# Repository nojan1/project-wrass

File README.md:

# Project Wrass

The purpose of Project Wrass is to develop the **Wrass 1**.

A 6502 based computer having the following specs.

* W65C02 running at 2Mhz
* Bankable RAM giving a total of approx 300KB of usable memory
* Expansion bus for up to 16 devices

> **Future specs**:  
>
> * VGA output of 640x480 with 256 colors
> * IO Card with W65C22 Vias and support for SPI
> * Support for SD cards on IO card
> * 8Mhz CPU clock speed
> * Global scroll registers for video
> * Sprites
> * 3 channel sound synthesizer

## Software

The 16KB ROM is bankable using an external switch. This allows the computer to run "2 sets" of software.

The existing one is a simple homebrew "monitor" giving access to simple read, write and jump commands.

> **Future**:  
> Support enhanced basic

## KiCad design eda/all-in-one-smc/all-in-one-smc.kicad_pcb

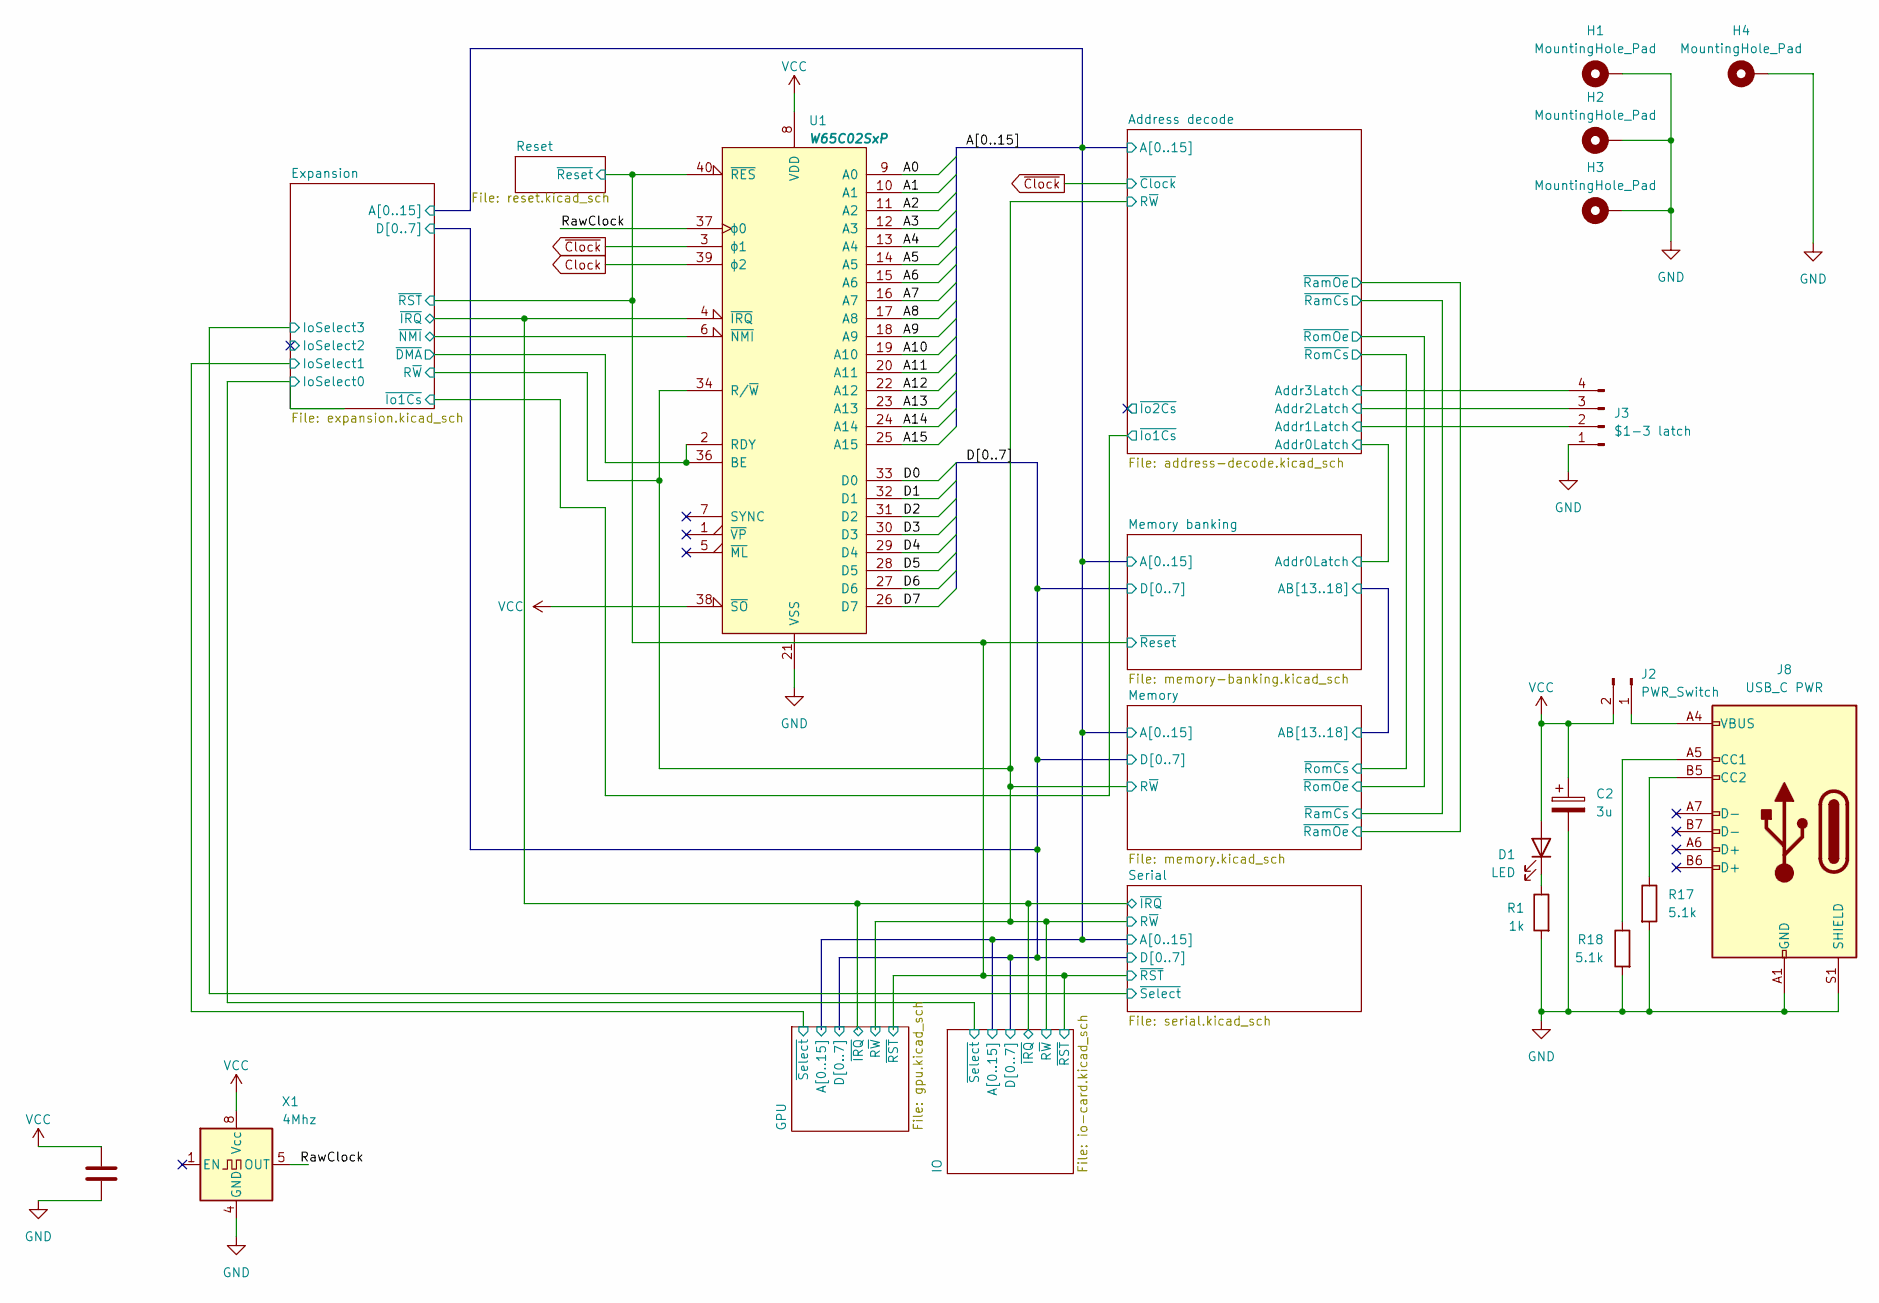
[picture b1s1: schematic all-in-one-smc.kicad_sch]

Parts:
C1: 100n; C_0805_2012Metric
C2: 3u; CP_Elec_8x5.4
D1: LED; LED_0805_2012Metric
H1, H2, H3, H4: MountingHole_Pad; MountingHole_2.5mm_Pad_Via
J2: PWR_Switch; PinHeader_1x02_P2.54mm_Vertical
J3: $1-3 latch; PinHeader_1x04_P2.54mm_Vertical
J8: USB_C PWR; USB_C_Receptacle_GCT_USB4105-xx-A_16P_TopMnt_Horizontal
R1: 1k; R_0805_2012Metric
R17, R18: 5.1k; R_0805_2012Metric
U1: W65C02SxP; PQFP-44_10x10mm_P0.8mm
X1: 4Mhz; Oscillator_DIP-8

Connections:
/A0: U1.9 (A0); also elsewhere on the board
/A1: U1.10 (A1); also elsewhere on the board
/A2: U1.11 (A2); also elsewhere on the board
/A3: U1.12 (A3); also elsewhere on the board
/A4: U1.13 (A4); also elsewhere on the board
/A5: U1.14 (A5); also elsewhere on the board
/A6: U1.15 (A6); also elsewhere on the board
/A7: U1.16 (A7); also elsewhere on the board
/A8: U1.17 (A8); also elsewhere on the board
/A9: U1.18 (A9); also elsewhere on the board
/A10: U1.19 (A10); also elsewhere on the board
/A11: U1.20 (A11); also elsewhere on the board
/A12: U1.22 (A12); also elsewhere on the board
/A13: U1.23 (A13); also elsewhere on the board
/A14: U1.24 (A14); also elsewhere on the board
/A15: U1.25 (A15); also elsewhere on the board
/Address decode/Addr1Latch: J3.2; also elsewhere on the board
/Address decode/Addr2Latch: J3.3; also elsewhere on the board
/Address decode/Addr3Latch: J3.4; also elsewhere on the board
/Address decode/R~W: U1.34 (R/~W); also elsewhere on the board
/D0: U1.33 (D0); also elsewhere on the board
/D1: U1.32 (D1); also elsewhere on the board
/D2: U1.31 (D2); also elsewhere on the board
/D3: U1.30 (D3); also elsewhere on the board
/D4: U1.29 (D4); also elsewhere on the board
/D5: U1.28 (D5); also elsewhere on the board
/D6: U1.27 (D6); also elsewhere on the board
/D7: U1.26 (D7); also elsewhere on the board
/Expansion/~DMA: U1.2 (RDY), U1.36 (BE); also elsewhere on the board
/Expansion/~IRQ: U1.4 (~IRQ); also elsewhere on the board
/Expansion/~NMI: U1.6 (~NMI); also elsewhere on the board
/Expansion/~RST: U1.40 (~RES); also elsewhere on the board
/RawClock: U1.37 (ϕ0), X1.5 (OUT)
Clock: U1.39 (ϕ2); also elsewhere on the board
unnamed: D1.1 (K), R1.1
unnamed: J2.1, J8.A4 (VBUS), J8.A9 (VBUS), J8.B4 (VBUS), J8.B9 (VBUS)
unnamed: J8.A5 (CC1), R18.1
unnamed: J8.B5 (CC2), R17.1
~Clock: U1.3 (ϕ1); also elsewhere on the board

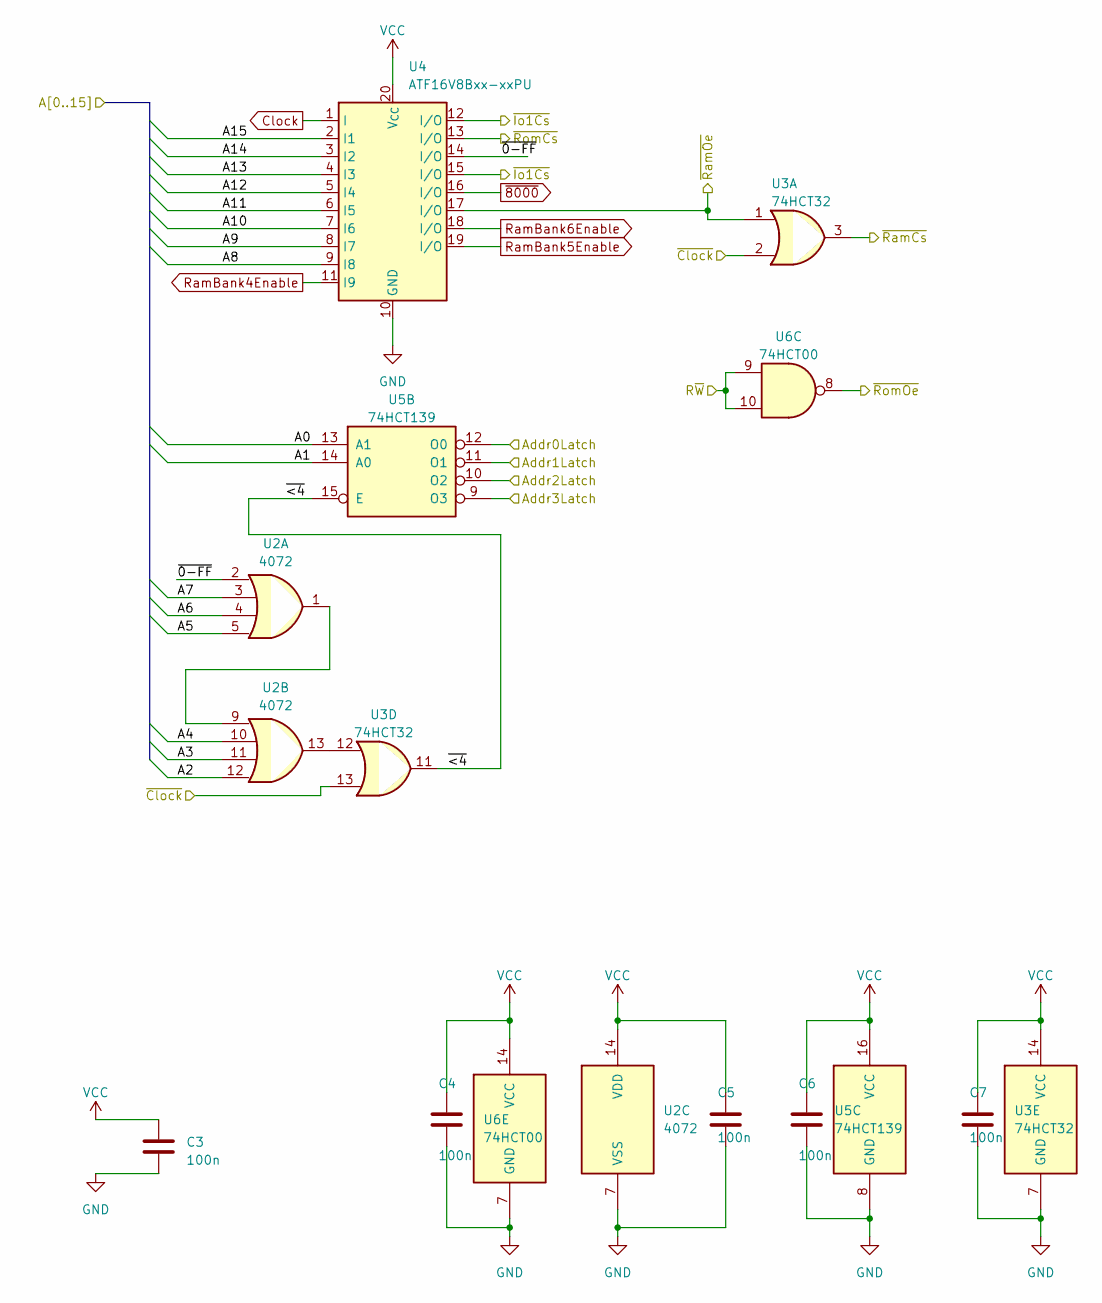
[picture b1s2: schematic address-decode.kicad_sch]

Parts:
C3, C4, C5, C6, C7: 100n; C_0805_2012Metric
U2: 4072; SOIC-14_3.9x8.7mm_P1.27mm
U3: 74HCT32; SOIC-14_3.9x8.7mm_P1.27mm
U4: ATF16V8Bxx-xxPU; DIP-20_W7.62mm_Socket
U5: 74HCT139; SOIC-16_3.9x9.9mm_P1.27mm
U6: 74HCT00; SOIC-14_3.9x8.7mm_P1.27mm

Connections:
/A0: U5.13 (A1); also elsewhere on the board
/A1: U5.14 (A0); also elsewhere on the board
/A2: U2.12; also elsewhere on the board
/A3: U2.11; also elsewhere on the board
/A4: U2.10; also elsewhere on the board
/A5: U2.5; also elsewhere on the board
/A6: U2.4; also elsewhere on the board
/A7: U2.3; also elsewhere on the board
/A8: U4.9 (I8); also elsewhere on the board
/A9: U4.8 (I7); also elsewhere on the board
/A10: U4.7 (I6); also elsewhere on the board
/A11: U4.6 (I5); also elsewhere on the board
/A12: U4.5 (I4); also elsewhere on the board
/A13: U4.4 (I3); also elsewhere on the board
/A14: U4.3 (I2); also elsewhere on the board
/A15: U4.2 (I1); also elsewhere on the board
/Address decode/Addr0Latch: U5.12 (O0); also elsewhere on the board
/Address decode/Addr1Latch: U5.11 (O1); also elsewhere on the board
/Address decode/Addr2Latch: U5.10 (O2); also elsewhere on the board
/Address decode/Addr3Latch: U5.9 (O3); also elsewhere on the board
/Address decode/R~W: U6.9, U6.10; also elsewhere on the board
/Address decode/~0-FF: U2.2, U4.14 (I/O)
/Address decode/~<4: U3.11, U5.15 (E)
/Address decode/~Io1Cs: U4.12 (I/O), U4.15 (I/O); also elsewhere on the board
/Address decode/~RamCs: U3.3; also elsewhere on the board
/Address decode/~RamOe: U3.1, U4.17 (I/O); also elsewhere on the board
/Address decode/~RomCs: U4.13 (I/O); also elsewhere on the board
/Address decode/~RomOe: U6.8; also elsewhere on the board
Clock: U4.1 (I); also elsewhere on the board
unnamed: U2.1, U2.9
unnamed: U2.13, U3.12
RamBank4Enable: U4.11 (I9); also elsewhere on the board
RamBank5Enable: U4.19 (I/O); also elsewhere on the board
RamBank6Enable: U4.18 (I/O); also elsewhere on the board
~8000: U4.16 (I/O); also elsewhere on the board
~Clock: U3.2, U3.13; also elsewhere on the board

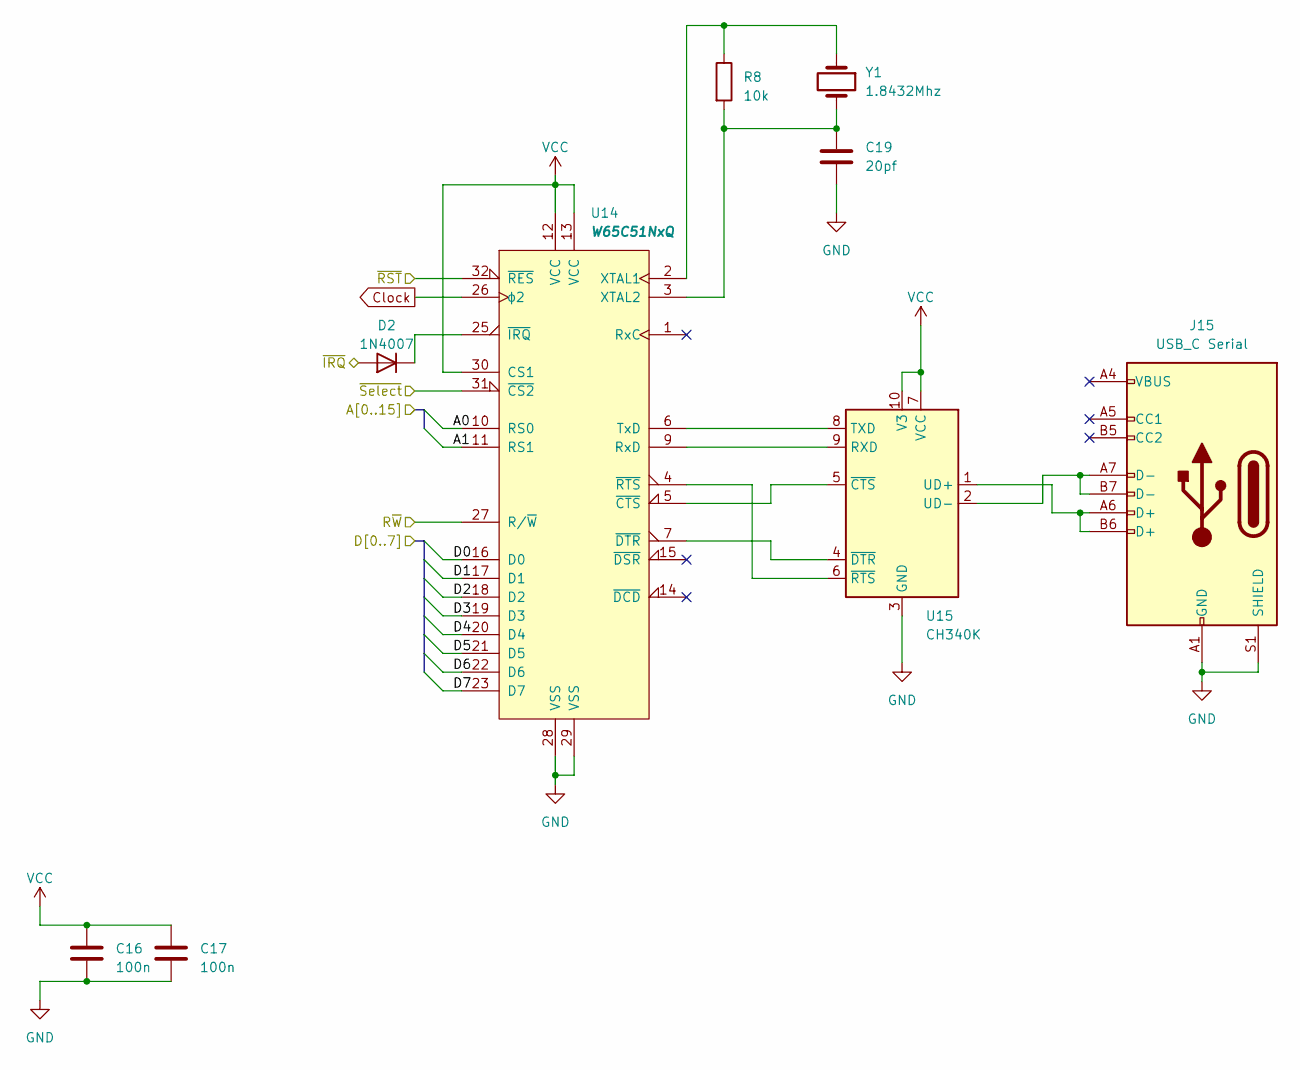
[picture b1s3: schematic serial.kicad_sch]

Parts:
C16, C17: 100n; C_0805_2012Metric
C19: 20pf; C_0805_2012Metric
D2: 1N4007; D_0805_2012Metric
J15: USB_C Serial; USB_C_Receptacle_GCT_USB4105-xx-A_16P_TopMnt_Horizontal
R8: 10k; R_0805_2012Metric
U14: W65C51NxQ; TQFP-32_7x7mm_P0.8mm
U15: CH340K; SSOP-10-1EP_3.9x4.9mm_P1mm_EP2.1x3.3mm
Y1: 1.8432Mhz; Crystal_SMD_3215-2Pin_3.2x1.5mm

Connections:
/A0: U14.10 (RS0); also elsewhere on the board
/A1: U14.11 (RS1); also elsewhere on the board
/Address decode/R~W: U14.27 (R/~W); also elsewhere on the board
/D0: U14.16 (D0); also elsewhere on the board
/D1: U14.17 (D1); also elsewhere on the board
/D2: U14.18 (D2); also elsewhere on the board
/D3: U14.19 (D3); also elsewhere on the board
/D4: U14.20 (D4); also elsewhere on the board
/D5: U14.21 (D5); also elsewhere on the board
/D6: U14.22 (D6); also elsewhere on the board
/D7: U14.23 (D7); also elsewhere on the board
/Expansion/IoSelect3: U14.31 (~CS2); also elsewhere on the board
/Expansion/~IRQ: D2.2 (A); also elsewhere on the board
/Expansion/~RST: U14.32 (~RES); also elsewhere on the board
Clock: U14.26 (ϕ2); also elsewhere on the board
unnamed: D2.1 (K), U14.25 (~IRQ)
unnamed: U14.9 (RxD), U15.9 (RXD)
unnamed: U14.6 (TxD), U15.8 (TXD)
unnamed: R8.1, U14.2 (XTAL1), Y1.1
unnamed: C19.1, R8.2, U14.3 (XTAL2), Y1.2
unnamed: U14.5 (~CTS), U15.5 (~CTS)
unnamed: U14.7 (~DTR), U15.4 (~DTR)
unnamed: U14.4 (~RTS), U15.6 (~RTS)
unnamed: J15.A6 (D+), J15.B6 (D+), U15.1 (UD+)
unnamed: J15.A7 (D-), J15.B7 (D-), U15.2 (UD-)

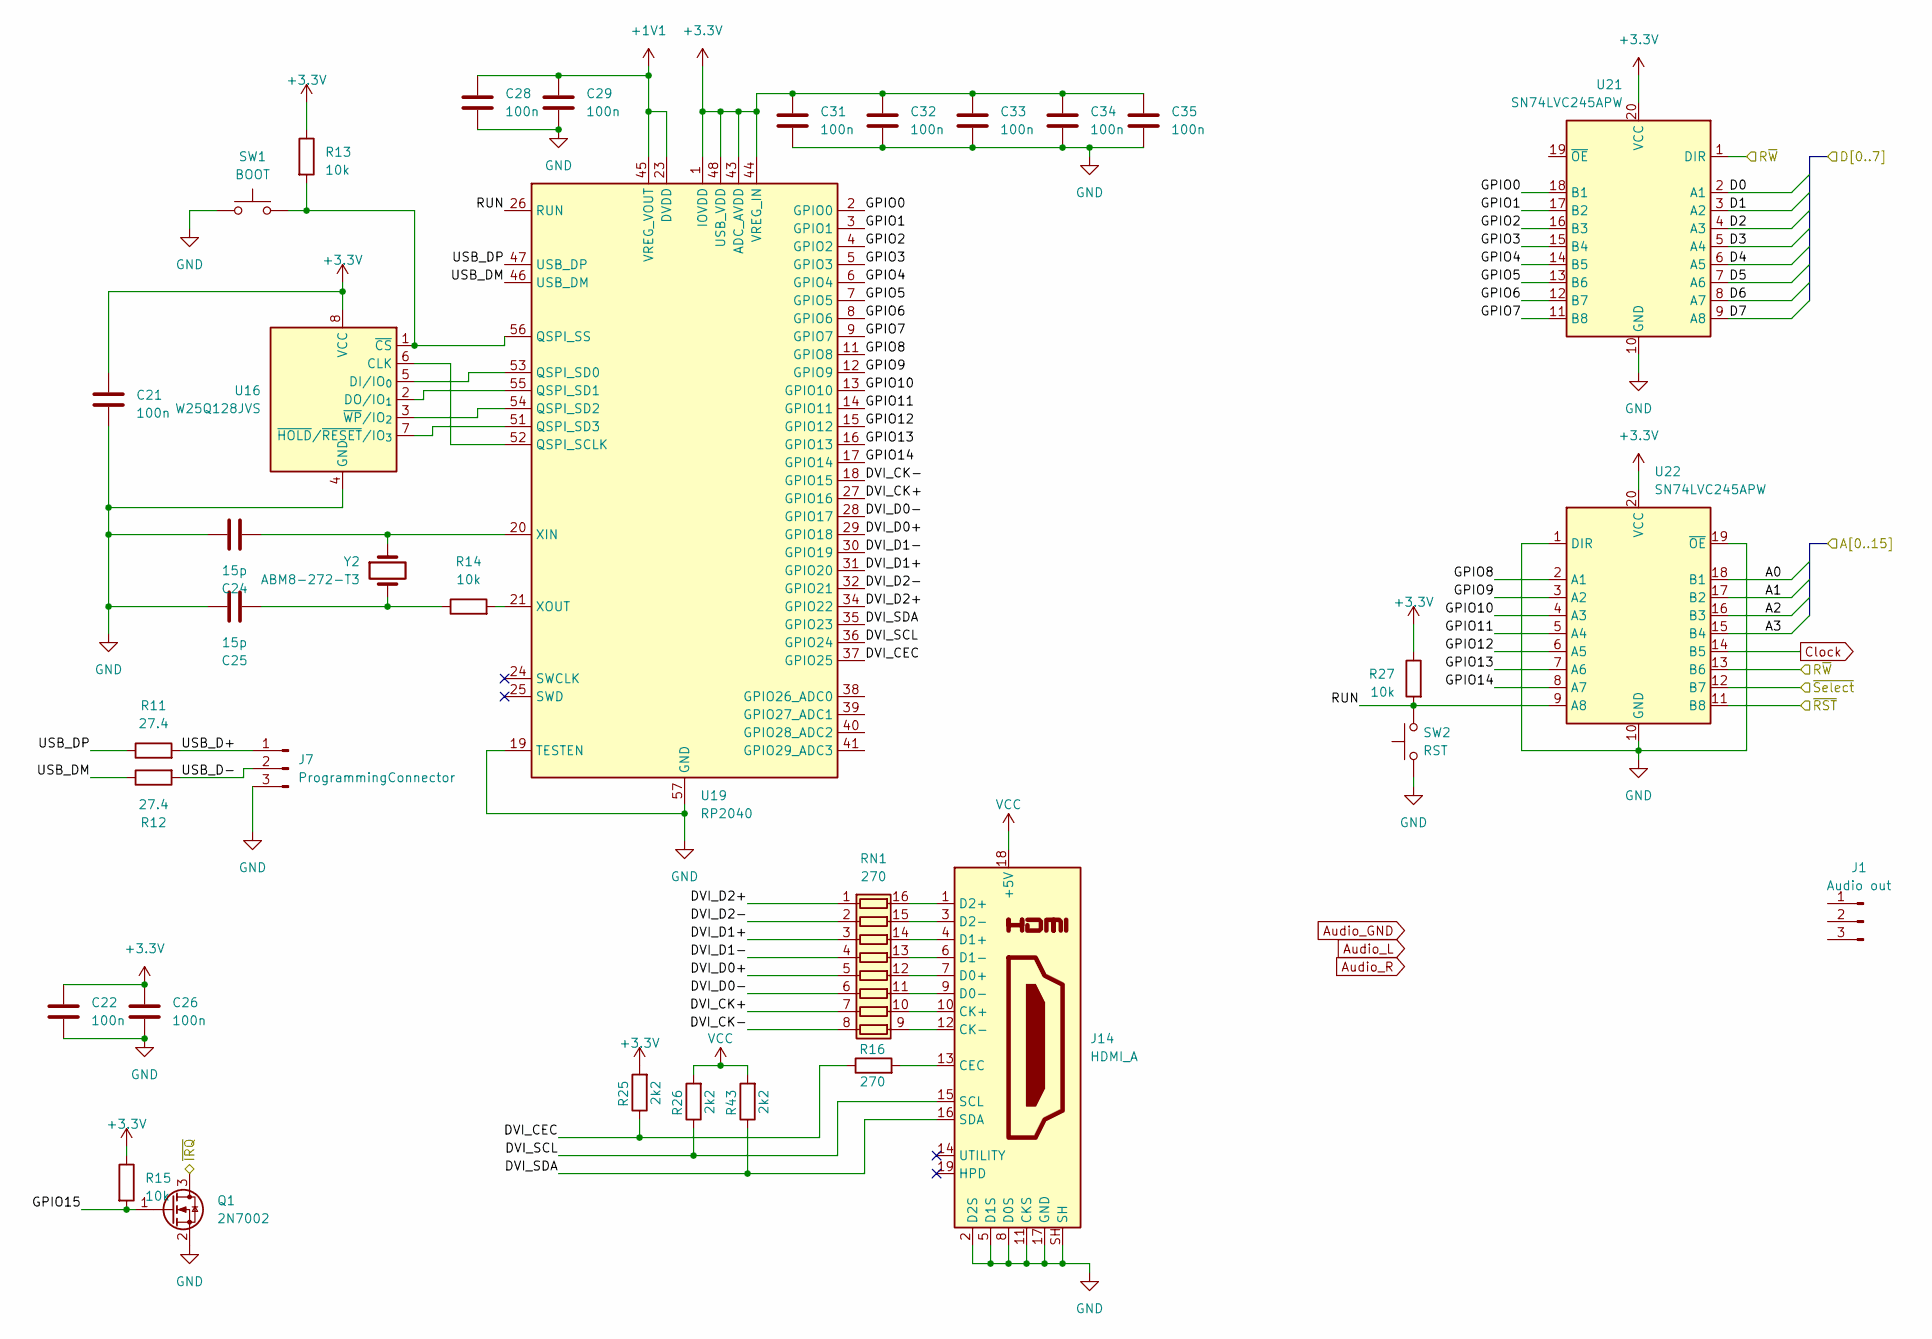
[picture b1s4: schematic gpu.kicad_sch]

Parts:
C21, C22, C26, C28, C29, C31, C32, C33, C34, C35: 100n; C_0805_2012Metric
C24, C25: 15p; C_0805_2012Metric
J1: Audio out; PinHeader_1x03_P2.54mm_Vertical
J7: ProgrammingConnector; PinHeader_1x03_P2.54mm_Vertical
J14: HDMI_A; HDMI_A_Molex_208658-1001_Horizontal
Q1: 2N7002; SOT-23
R11, R12: 27.4; R_0805_2012Metric
R13, R14, R15, R27: 10k; R_0805_2012Metric
R16: 270; R_0805_2012Metric
R25, R26, R43: 2k2; R_0805_2012Metric
RN1: 270; R_Array_Convex_8x0602
SW1: BOOT; SW_Push_1P1T_NO_CK_KMR2
SW2: RST; SW_Push_1P1T_NO_CK_KMR2
U16: W25Q128JVS; SOIC-8_5.3x5.3mm_P1.27mm
U19: RP2040; QFN-56-1EP_7x7mm_P0.4mm_EP3.2x3.2mm
U21, U22: SN74LVC245APW; TSSOP-20_4.4x6.5mm_P0.65mm
Y2: ABM8-272-T3; Crystal_SMD_Abracon_ABM8AIG-4Pin_3.2x2.5mm

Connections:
+1V1: C28.1, C29.1, U19.23 (DVDD), U19.45 (VREG_VOUT), U19.50 (DVDD)
/A0: U22.18 (B1); also elsewhere on the board
/A1: U22.17 (B2); also elsewhere on the board
/A2: U22.16 (B3); also elsewhere on the board
/A3: U22.15 (B4); also elsewhere on the board
/Address decode/R~W: U21.1 (DIR), U22.13 (B6); also elsewhere on the board
/D0: U21.2 (A1); also elsewhere on the board
/D1: U21.3 (A2); also elsewhere on the board
/D2: U21.4 (A3); also elsewhere on the board
/D3: U21.5 (A4); also elsewhere on the board
/D4: U21.6 (A5); also elsewhere on the board
/D5: U21.7 (A6); also elsewhere on the board
/D6: U21.8 (A7); also elsewhere on the board
/D7: U21.9 (A8); also elsewhere on the board
/Expansion/IoSelect1: U22.12 (B7); also elsewhere on the board
/Expansion/~RST: U22.11 (B8); also elsewhere on the board
/GPU/DVI_CEC: R16.1, R25.1, U19.37 (GPIO25)
/GPU/DVI_CK+: RN1.7 (R7.1), U19.27 (GPIO16)
/GPU/DVI_CK-: RN1.8 (R8.1), U19.18 (GPIO15)
/GPU/DVI_D0+: RN1.5 (R5.1), U19.29 (GPIO18)
/GPU/DVI_D0-: RN1.6 (R6.1), U19.28 (GPIO17)
/GPU/DVI_D1+: RN1.3 (R3.1), U19.31 (GPIO20)
/GPU/DVI_D1-: RN1.4 (R4.1), U19.30 (GPIO19)
/GPU/DVI_D2+: RN1.1 (R1.1), U19.34 (GPIO22)
/GPU/DVI_D2-: RN1.2 (R2.1), U19.32 (GPIO21)
/GPU/DVI_SCL: J14.15 (SCL), R26.1, U19.36 (GPIO24)
/GPU/DVI_SDA: J14.16 (SDA), R43.1, U19.35 (GPIO23)
/GPU/GPIO0: U19.2 (GPIO0), U21.18 (B1)
/GPU/GPIO1: U19.3 (GPIO1), U21.17 (B2)
/GPU/GPIO2: U19.4 (GPIO2), U21.16 (B3)
/GPU/GPIO3: U19.5 (GPIO3), U21.15 (B4)
/GPU/GPIO4: U19.6 (GPIO4), U21.14 (B5)
/GPU/GPIO5: U19.7 (GPIO5), U21.13 (B6)
/GPU/GPIO6: U19.8 (GPIO6), U21.12 (B7)
/GPU/GPIO7: U19.9 (GPIO7), U21.11 (B8)
/GPU/GPIO8: U19.11 (GPIO8), U22.2 (A1)
/GPU/GPIO9: U19.12 (GPIO9), U22.3 (A2)
/GPU/GPIO10: U19.13 (GPIO10), U22.4 (A3)
/GPU/GPIO11: U19.14 (GPIO11), U22.5 (A4)
/GPU/GPIO12: U19.15 (GPIO12), U22.6 (A5)
/GPU/GPIO13: U19.16 (GPIO13), U22.7 (A6)
/GPU/GPIO14: U19.17 (GPIO14), U22.8 (A7)
/GPU/GPIO15: Q1.1 (G), R15.2
/GPU/RUN: R27.2, SW2.2, U19.26 (RUN), U22.9 (A8)
/GPU/USB_D+: J7.1, R11.2
/GPU/USB_D-: J7.2, R12.2
/GPU/USB_DM: R12.1, U19.46 (USB_DM)
/GPU/USB_DP: R11.1, U19.47 (USB_DP)
/GPU/~IRQ: Q1.3 (D)
Clock: U22.14 (B5); also elsewhere on the board
unnamed: C25.1, R14.1, Y2.2
unnamed: J14.13 (CEC), R16.2
unnamed: J14.10 (CK+), RN1.10 (R7.2)
unnamed: J14.12 (CK-), RN1.9 (R8.2)
unnamed: J14.7 (D0+), RN1.12 (R5.2)
unnamed: J14.9 (D0-), RN1.11 (R6.2)
unnamed: J14.4 (D1+), RN1.14 (R3.2)
unnamed: J14.6 (D1-), RN1.13 (R4.2)
unnamed: J14.1 (D2+), RN1.16 (R1.2)
unnamed: J14.3 (D2-), RN1.15 (R2.2)
unnamed: U16.6 (CLK), U19.52 (QSPI_SCLK)
unnamed: U16.5 (DI/IO_{0}), U19.53 (QSPI_SD0)
unnamed: U16.2 (DO/IO_{1}), U19.55 (QSPI_SD1)
unnamed: R13.2, SW1.2, U16.1 (~CS), U19.56 (QSPI_SS)
unnamed: U16.7 (~HOLD/~RESET/IO_{3}), U19.51 (QSPI_SD3)
unnamed: U16.3 (~WP/IO_{2}), U19.54 (QSPI_SD2)
unnamed: C24.1, U19.20 (XIN), Y2.1
unnamed: R14.2, U19.21 (XOUT)

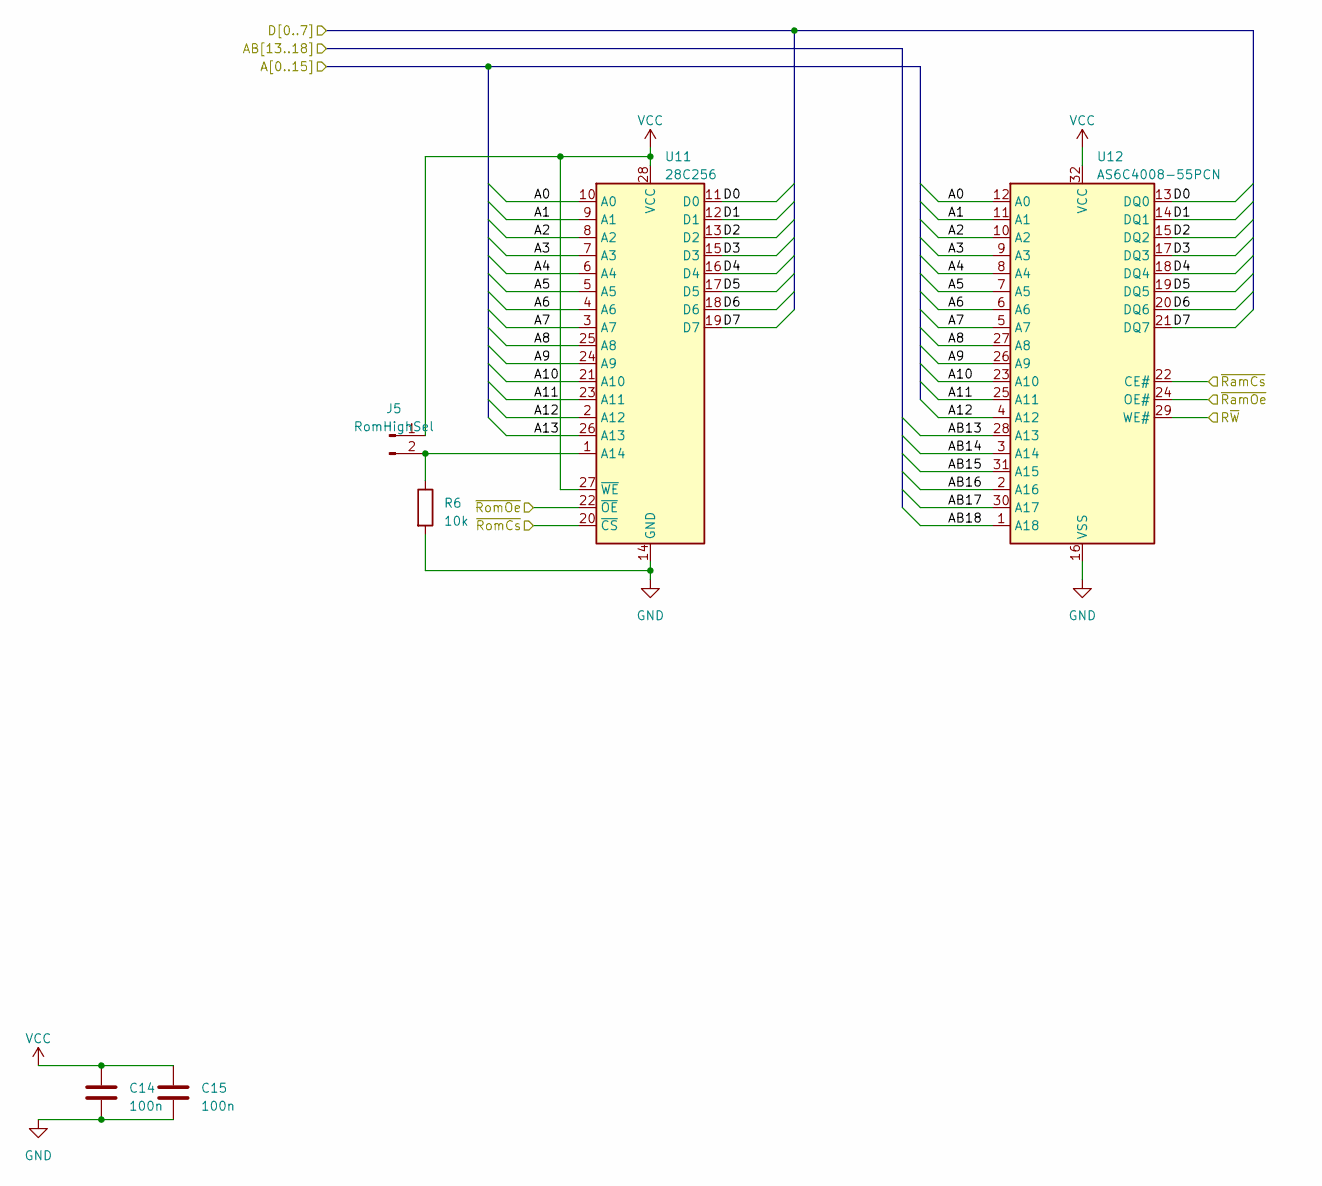
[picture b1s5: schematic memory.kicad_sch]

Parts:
C14, C15: 100n; C_0805_2012Metric
J5: RomHighSel; PinHeader_1x02_P2.54mm_Vertical
R6: 10k; R_0805_2012Metric
U11: 28C256; DIP-28_W15.24mm_Socket_LongPads
U12: AS6C4008-55PCN; SOIC-32_7.518x20.777mm_P1.27mm

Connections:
/A0: U11.10 (A0), U12.12 (A0); also elsewhere on the board
/A1: U11.9 (A1), U12.11 (A1); also elsewhere on the board
/A2: U11.8 (A2), U12.10 (A2); also elsewhere on the board
/A3: U11.7 (A3), U12.9 (A3); also elsewhere on the board
/A4: U11.6 (A4), U12.8 (A4); also elsewhere on the board
/A5: U11.5 (A5), U12.7 (A5); also elsewhere on the board
/A6: U11.4 (A6), U12.6 (A6); also elsewhere on the board
/A7: U11.3 (A7), U12.5 (A7); also elsewhere on the board
/A8: U11.25 (A8), U12.27 (A8); also elsewhere on the board
/A9: U11.24 (A9), U12.26 (A9); also elsewhere on the board
/A10: U11.21 (A10), U12.23 (A10); also elsewhere on the board
/A11: U11.23 (A11), U12.25 (A11); also elsewhere on the board
/A12: U11.2 (A12), U12.4 (A12); also elsewhere on the board
/A13: U11.26 (A13); also elsewhere on the board
/Address decode/R~W: U12.29 (WE#); also elsewhere on the board
/Address decode/~RamCs: U12.22 (CE#); also elsewhere on the board
/Address decode/~RamOe: U12.24 (OE#); also elsewhere on the board
/Address decode/~RomCs: U11.20 (~CS); also elsewhere on the board
/Address decode/~RomOe: U11.22 (~OE); also elsewhere on the board
/D0: U11.11 (D0), U12.13 (DQ0); also elsewhere on the board
/D1: U11.12 (D1), U12.14 (DQ1); also elsewhere on the board
/D2: U11.13 (D2), U12.15 (DQ2); also elsewhere on the board
/D3: U11.15 (D3), U12.17 (DQ3); also elsewhere on the board
/D4: U11.16 (D4), U12.18 (DQ4); also elsewhere on the board
/D5: U11.17 (D5), U12.19 (DQ5); also elsewhere on the board
/D6: U11.18 (D6), U12.20 (DQ6); also elsewhere on the board
/D7: U11.19 (D7), U12.21 (DQ7); also elsewhere on the board
/Memory banking/AB13: U12.28 (A13); also elsewhere on the board
/Memory banking/AB14: U12.3 (A14); also elsewhere on the board
/Memory banking/AB15: U12.31 (A15); also elsewhere on the board
/Memory banking/AB16: U12.2 (A16); also elsewhere on the board
/Memory banking/AB17: U12.30 (A17); also elsewhere on the board
/Memory banking/AB18: U12.1 (A18); also elsewhere on the board
unnamed: J5.2, R6.1, U11.1 (A14)

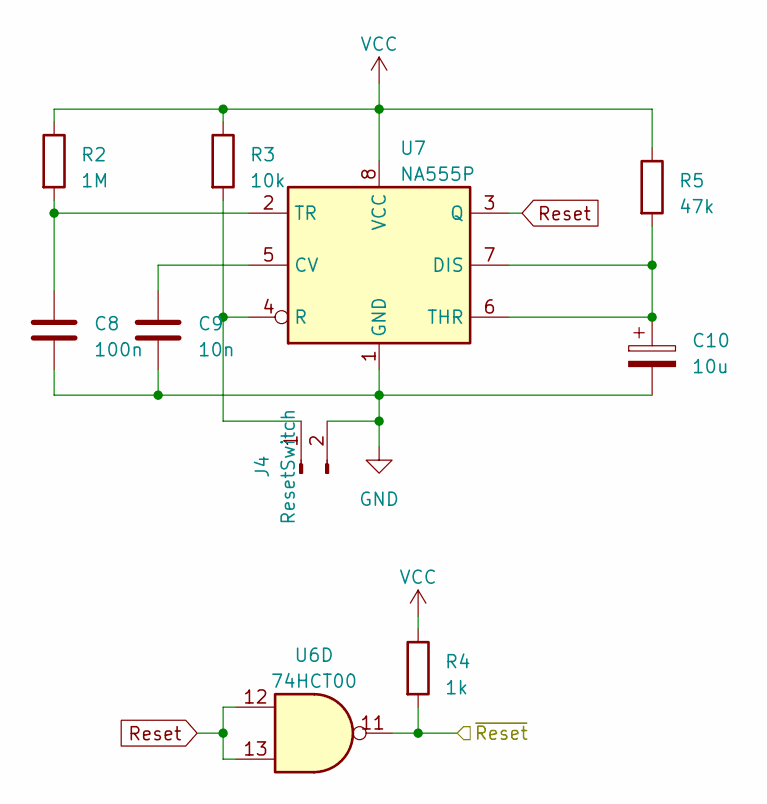
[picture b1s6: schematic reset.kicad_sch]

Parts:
C8: 100n; C_0805_2012Metric
C9: 10n; C_0805_2012Metric
C10: 10u; CP_Elec_4x3
J4: ResetSwitch; PinHeader_1x02_P2.54mm_Vertical
R2: 1M; R_0805_2012Metric
R3: 10k; R_0805_2012Metric
R4: 1k; R_0805_2012Metric
R5: 47k; R_0805_2012Metric
U6: 74HCT00; SOIC-14_3.9x8.7mm_P1.27mm
U7: NA555P; SOIC-8_3.9x4.9mm_P1.27mm

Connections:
/Expansion/~RST: R4.2, U6.11; also elsewhere on the board
unnamed: J4.1, R3.2, U7.4 (R)
unnamed: C9.1, U7.5 (CV)
unnamed: C10.1, R5.2, U7.6 (THR), U7.7 (DIS)
unnamed: C8.1, R2.2, U7.2 (TR)
Reset: U6.12, U6.13, U7.3 (Q)

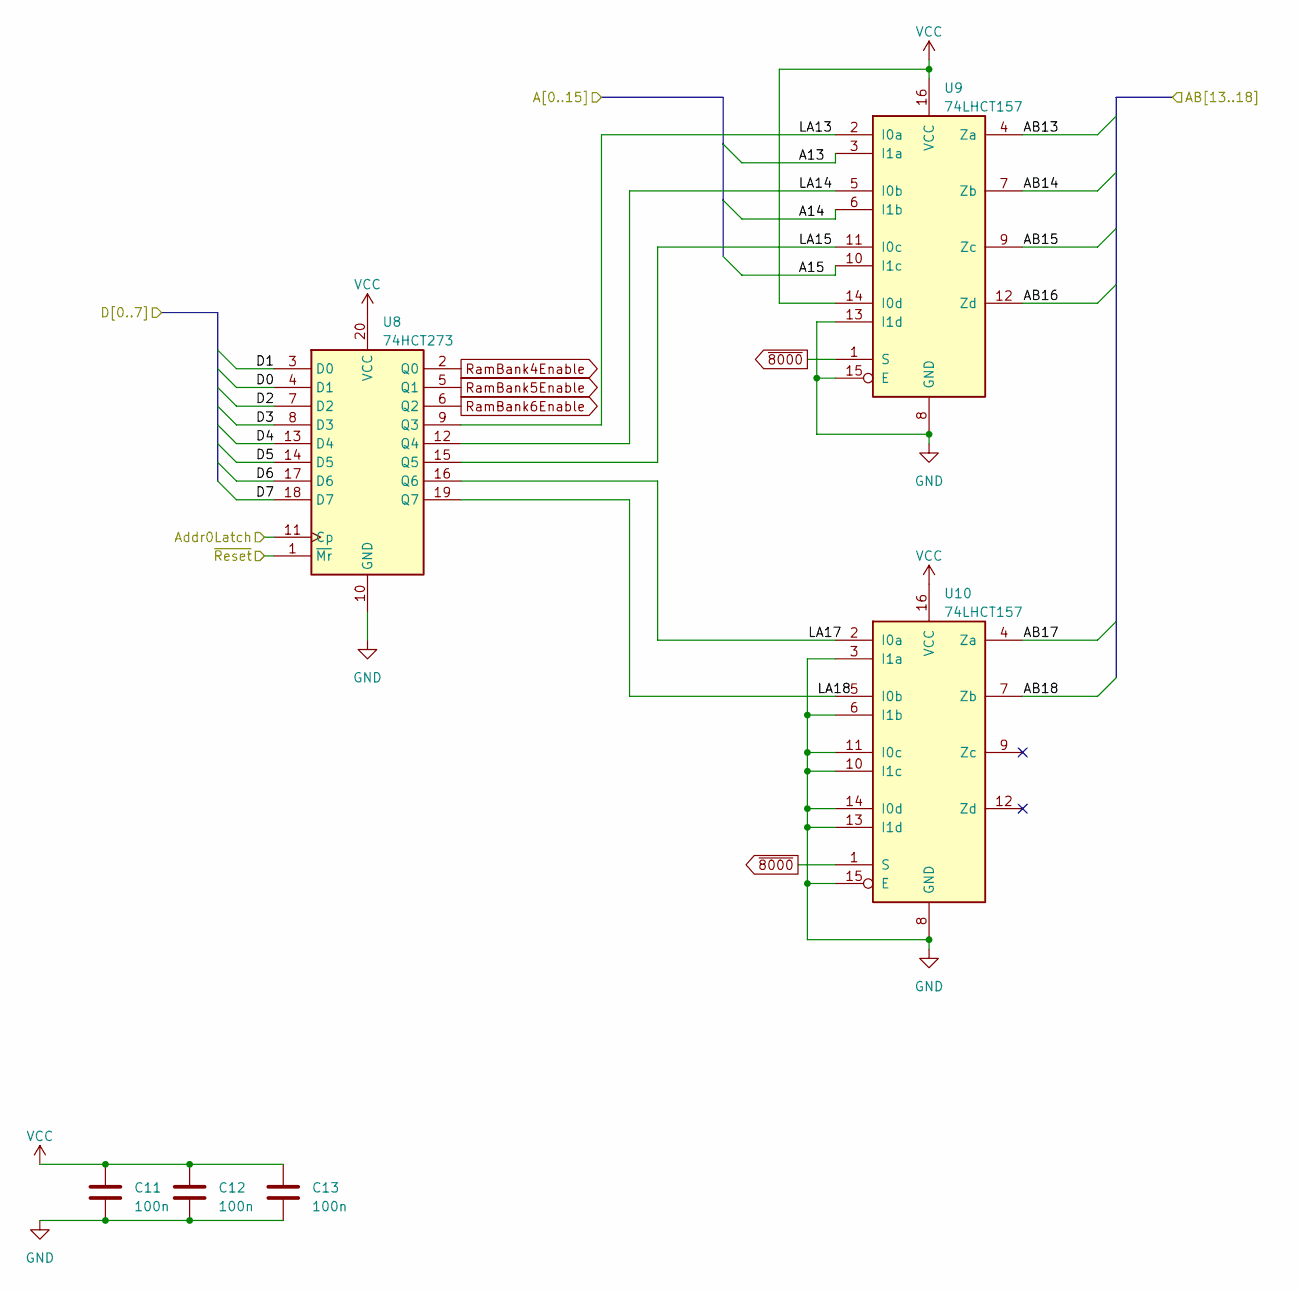
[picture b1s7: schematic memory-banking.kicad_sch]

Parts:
C11, C12, C13: 100n; C_0805_2012Metric
U8: 74HCT273; SOIC-20W_7.5x12.8mm_P1.27mm
U9, U10: 74LHCT157; SOIC-16_3.9x9.9mm_P1.27mm

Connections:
/A13: U9.3 (I1a); also elsewhere on the board
/A14: U9.6 (I1b); also elsewhere on the board
/A15: U9.10 (I1c); also elsewhere on the board
/Address decode/Addr0Latch: U8.11 (Cp); also elsewhere on the board
/D0: U8.4 (D1); also elsewhere on the board
/D1: U8.3 (D0); also elsewhere on the board
/D2: U8.7 (D2); also elsewhere on the board
/D3: U8.8 (D3); also elsewhere on the board
/D4: U8.13 (D4); also elsewhere on the board
/D5: U8.14 (D5); also elsewhere on the board
/D6: U8.17 (D6); also elsewhere on the board
/D7: U8.18 (D7); also elsewhere on the board
/Expansion/~RST: U8.1 (~Mr); also elsewhere on the board
/Memory banking/AB13: U9.4 (Za); also elsewhere on the board
/Memory banking/AB14: U9.7 (Zb); also elsewhere on the board
/Memory banking/AB15: U9.9 (Zc); also elsewhere on the board
/Memory banking/AB16: U9.12 (Zd); also elsewhere on the board
/Memory banking/AB17: U10.4 (Za); also elsewhere on the board
/Memory banking/AB18: U10.7 (Zb); also elsewhere on the board
/Memory banking/LA13: U8.9 (Q3), U9.2 (I0a)
/Memory banking/LA14: U8.12 (Q4), U9.5 (I0b)
/Memory banking/LA15: U8.15 (Q5), U9.11 (I0c)
/Memory banking/LA17: U8.16 (Q6), U10.2 (I0a)
/Memory banking/LA18: U8.19 (Q7), U10.5 (I0b)
RamBank4Enable: U8.2 (Q0); also elsewhere on the board
RamBank5Enable: U8.5 (Q1); also elsewhere on the board
RamBank6Enable: U8.6 (Q2); also elsewhere on the board
~8000: U9.1 (S), U10.1 (S); also elsewhere on the board
